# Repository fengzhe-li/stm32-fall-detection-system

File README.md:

# STM32-Based Elderly Fall Detection and Health Monitoring System

A wearable safety device built on the **STM32F103C8T6**: it detects falls via accelerometer, monitors heart rate / SpO₂ / body temperature, and automatically sends an SMS alert with GPS location to a caregiver. Includes a manual SOS button, on-device threshold configuration, and remote SMS commands.

---

## 🎥 Physical Prototype Demonstration

▶️ **[Watch the physical prototype video](docs/videos/physical-prototype.mp4)**

The assembled hardware in operation — OLED display, sensors, GSM/GPS modules, keypad, and a physical fall/recovery cycle with the resulting alert behavior. This is historical evidence from the original build; see [Validation](#-validation) for what it does and does not confirm about the current firmware.

---

## 📌 Overview

The system integrates multiple sensors to monitor an elderly user's physiological state and motion in real time. On a fall or an abnormal vital sign, it sounds a local buzzer and sends an SMS alert containing current vitals and GPS coordinates. A short, fixed confirmation delay after a detected fall gives the wearer a chance to recover or cancel before the alert is sent.

## ⚙️ Features

- Fall detection with hysteresis (separate entry/recovery thresholds) and a fixed confirmation delay before alerting
- Automatic SMS alert on fall, abnormal heart rate, abnormal SpO₂, abnormal temperature, or manual SOS — each tracked independently
- GPS location embedded in every alert (hemisphere-aware coordinate sign)
- Cancel/acknowledge button that silences the buzzer and suppresses the current fall alert, without disabling future fall detection
- On-device OLED UI for live vitals, threshold configuration, and phone-number entry
- Remote SMS commands: request current data on demand, set the alert phone number remotely
- Persistent phone-number storage across power cycles (on-chip Flash)

## 🧩 Firmware & Architecture

Firmware source is available under [`firmware/`](firmware/) (`User/`, `Libraries/`, `Project/` — Keil MDK / ARM Compiler 5, ST Standard Peripheral Library, no HAL/RTOS).

Full architecture write-up — hardware modules, super-loop/interrupt structure, and the fall / health-alert / SOS-cancel flows — is in **[`docs/architecture.md`](docs/architecture.md)**.

## 🔧 Engineering Improvements

The recovered source underwent a memory-safety and control-logic hardening pass: Flash byte/halfword correction, UART/GPS receive-buffer protection, safer coordinate formatting, a GPS hemisphere-sign fix, a MAX30102 divide-by-zero guard, a cancel-alarm control-logic correction, and a bounded GSM startup retry.

Full write-up: **[`docs/engineering-improvements.md`](docs/engineering-improvements.md)**.

## ✅ Validation

Two distinct kinds of evidence exist for this project — **historical physical/simulation validation** of the original build, and **current host-side automated verification** (Clang + ASan/UBSan) of the hardening work above. They are kept clearly separate, and the hardened firmware has **not** yet been rebuilt in Keil, flashed, or re-validated on the physical device.

Full breakdown: **[`docs/validation.md`](docs/validation.md)**.

---

## 🧪 Experimental Results

| Working state | Fall & recovery | Heart-rate sensor active |
|---|---|---|
|  |  |  |

**SMS alerts received:**

| Fall | SOS / help | Heart rate | Blood oxygen | Temperature |
|---|---|---|---|---|
|  |  |  |  |  |

**On-device threshold settings:**

| Heart rate | Blood oxygen | Body temperature | Phone number |
|---|---|---|---|
|  |  |  |  |

## 📍 GPS Positioning Test

Indoor environments cannot receive satellite signals, so latitude/longitude cannot be displayed indoors; in open outdoor environments, GPS coordinates are obtained normally.

## 🖥️ Proteus Simulation

▶️ **[Watch the Proteus simulation video](docs/videos/proteus-simulation.mp4)**  ·  

## 🔌 Circuit / Architecture References

| Circuit schematic | GSM & GPS display | SIM800 power supply |
|---|---|---|
|  |  |  |

## 🧭 Original PCB Layout

This is a screenshot of the original PCB layout created in the design software for the final prototype and preserved in Figure 13 of the dissertation.

---

## 📂 Repository Structure

```
stm32-fall-detection-system/
├── README.md
├── firmware/            # STM32 firmware source (User, Libraries, Project — Keil MDK)
├── hardware/            # Schematic / PCB design files (reference only, see notice below)
├── bom/                 # Bill of materials
├── docs/
│   ├── images/          # Photos, PCB evidence, OLED/UI, and SMS alert screenshots
│   ├── videos/          # Physical prototype + Proteus simulation videos
│   ├── architecture.md
│   ├── validation.md
│   ├── engineering-improvements.md
│   └── U2180177 Li Fengzhe Final report.pdf
└── tests/               # Host-side verification scripts (Clang + ASan/UBSan)
```

## ⚠️ Hardware Files Notice

The `hardware/` folder contains schematic and PCB design files created during development. The dissertation PCB figure above provides direct visual evidence of the final board arrangement. The supplied engineering files should be checked against the dissertation figure and photographed prototype before fabrication.

## 📦 Bill of Materials

Component list: [`bom/list.xlsx`](bom/list.xlsx)

## 📄 Project Report

Full project dissertation: [`docs/U2180177 Li Fengzhe Final report.pdf`](docs/U2180177%20Li%20Fengzhe%20Final%20report.pdf)

## 👨‍💻 Author

**Fengzhe Li** — Embedded Systems | STM32 | IoT

## Reconstructed final-style PCB

**Reconstructed Design Based on the Final Physical Prototype — Not Fabrication-Validated.** The editable KiCad project is in [`hardware/reconstructed-final/Reconstructed_Final_Design/`](hardware/reconstructed-final/Reconstructed_Final_Design/). It contains a symbol-and-wire schematic, routed two-layer PCB, explicit connectivity/BOM evidence and engineering front/back previews. Native KiCad ERC/DRC and 3D outputs are produced by the reconstruction validation workflow and remain subject to review.

The layout follows the genuine [prototype photograph](docs/images/Photograph%20of%20the%20device.jpg): central Blue Pill, GPS/OLED at left, SIM800 at upper-right, sensors below and five buttons at lower-right. Recovered CAD files are supporting historical evidence and remain unchanged. See the [reconstruction report](hardware/reconstructed-final/Reconstructed_Final_Design/RECONSTRUCTION_REPORT.md), [firmware-to-net mapping](hardware/reconstructed-final/Reconstructed_Final_Design/firmware_to_net_mapping.csv) and [verification results](hardware/reconstructed-final/Reconstructed_Final_Design/verification_results.md).

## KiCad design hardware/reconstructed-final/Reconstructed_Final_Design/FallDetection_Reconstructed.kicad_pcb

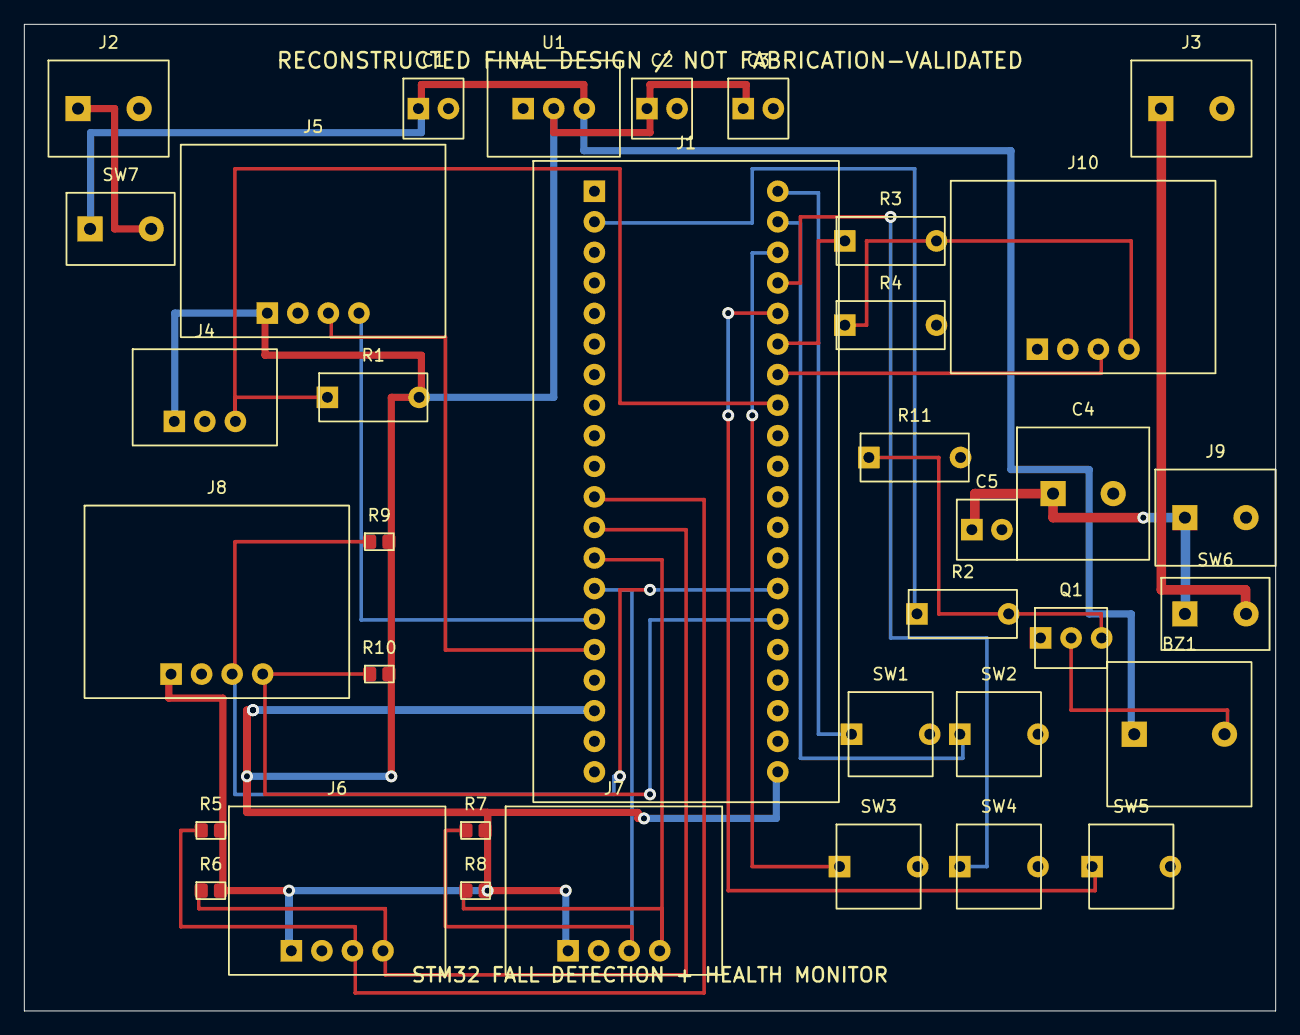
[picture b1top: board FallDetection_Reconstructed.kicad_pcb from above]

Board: 2 copper layers, 104.0 x 82.0 mm, 36 parts (0 on the bottom side), 26 nets.

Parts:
BZ1: 5 V active buzzer; buzzer_2P
C1: 10 uF regulator input; capacitor_2P
C2: 10 uF regulator output; capacitor_2P
C3: 100 nF regulator bypass; capacitor_2P
C4: 1000 uF low-ESR SIM800 bulk; capacitor_large_2P
C5: 100 nF SIM800 bypass; capacitor_2P
J1: STM32F103C8T6 Blue Pill socket; controller_40P
J2: Main 5 V input; power_2P
J3: SIM800 4.0 V input; power_2P
J4: DS18B20 module; temp_sensor_3P
J5: VK2828U7G5LF GPS module; module_4P
J6: ADXL345 breakout; sensor_4P
J7: MAX30102 breakout; sensor_4P
J8: 0.96 inch OLED I2C module; module_4P
J9: SIM800 power header; power_2P
J10: SIM800 UART / PWRKEY header; module_4P
Q1: S8050 low-side buzzer driver; transistor_3P
R1: 4.7k DS18B20 pull-up (DNP if module fitted); resistor_2P
R2: 1k buzzer base resistor; resistor_2P
R3: 10k SIM800 RX divider upper; resistor_2P
R4: 47k SIM800 RX divider lower; resistor_2P
R5: 4.7k ADXL SCL pull-up (DNP); resistor_smd_2P
R6: 4.7k ADXL SDA pull-up (DNP); resistor_smd_2P
R7: 4.7k MAX SCL pull-up (DNP); resistor_smd_2P
R8: 4.7k MAX SDA pull-up (DNP); resistor_smd_2P
R9: 4.7k OLED SCL pull-up (DNP); resistor_smd_2P
R10: 4.7k OLED SDA pull-up (DNP); resistor_smd_2P
R11: 10k buzzer base pull-down; resistor_2P
SW1: Mode button; button_2P
SW2: Up button; button_2P
SW3: Down button; button_2P
SW4: Next button; button_2P
SW5: Help button; button_2P
SW6: GSM VBAT switch; switch_2P
SW7: Main power switch; switch_2P
U1: AMS1117-3.3 regulator module; regulator_3P

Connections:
3V3: C2.1, C3.1, J1.18, J1.40, J4.1, J5.1, J6.1, J7.1, J8.1, R1.2, R5.2, R6.2, R7.2, R8.2, R9.2, R10.2, U1.2
+5V: BZ1.1, C1.1, SW7.1, U1.3
+5V_INPUT: J2.1, SW7.2
ACCEL_SCL_PA6: J1.11, J6.3, R5.1
ACCEL_SDA_PA7: J1.12, J6.4, R6.1
BTN_DOWN_PB14: J1.23, SW3.1
BTN_HELP_PA8: J1.25, SW5.1
BTN_MODE_PB12: J1.21, SW1.1
BTN_NEXT_PB15: J1.24, SW4.1
BTN_UP_PB13: J1.22, SW2.1
BUZZER_BASE: Q1.3, R2.2, R11.1
BUZZER_LOW_SIDE: BZ1.2, Q1.2
BUZZER_PC13: J1.2, R2.1
GND: C1.2, C2.2, C3.2, C4.2, C5.2, J1.19, J1.20, J1.39, J2.2, J3.2, J4.2, J5.2, J6.2, J7.2, J8.2, J9.2, J10.2, Q1.1, R4.2, R11.2, SW1.2, SW2.2, SW3.2, SW4.2, SW5.2, U1.1
GPS_RX_FROM_MCU_TX_PB10: J1.15, J5.4
GPS_TX_TO_MCU_RX_PB11: J1.16, J5.3
GSM_RX_DIVIDED: J10.4, R3.2, R4.1
GSM_TX_FROM_MCU_PA9: J1.26, R3.1
GSM_TX_TO_MCU_RX_PA10: J1.27, J10.3
MAX_SCL_PB1: J1.14, J7.3, R7.1
MAX_SDA_PB0: J1.13, J7.4, R8.1
OLED_SCL_PB6: J1.34, J8.3, R9.1
OLED_SDA_PB7: J1.35, J8.4, R10.1
SIM_VBAT: C4.1, C5.1, J9.1, SW6.1
SIM_VBAT_INPUT: J3.1, SW6.2
TEMP_DQ_PA11: J1.28, J4.3, R1.1

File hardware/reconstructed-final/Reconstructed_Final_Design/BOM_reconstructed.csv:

Reference,Component / module,Qty,Footprint,Population,Evidence / assumption
J1,STM32F103C8T6 Blue Pill socket,1,Reconstruction:controller_40P,Populate,See RECONSTRUCTION_REPORT.md; module dimensions and connector pin order require build review.
J2,Main 5 V input,1,Reconstruction:power_2P,Populate,See RECONSTRUCTION_REPORT.md; module dimensions and connector pin order require build review.
J3,SIM800 4.0 V input,1,Reconstruction:power_2P,Populate,See RECONSTRUCTION_REPORT.md; module dimensions and connector pin order require build review.
J4,DS18B20 module,1,Reconstruction:temp_sensor_3P,Populate,See RECONSTRUCTION_REPORT.md; module dimensions and connector pin order require build review.
J5,VK2828U7G5LF GPS module,1,Reconstruction:module_4P,Populate,See RECONSTRUCTION_REPORT.md; module dimensions and connector pin order require build review.
J6,ADXL345 breakout,1,Reconstruction:sensor_4P,Populate,See RECONSTRUCTION_REPORT.md; module dimensions and connector pin order require build review.
J7,MAX30102 breakout,1,Reconstruction:sensor_4P,Populate,See RECONSTRUCTION_REPORT.md; module dimensions and connector pin order require build review.
J8,0.96 inch OLED I2C module,1,Reconstruction:module_4P,Populate,See RECONSTRUCTION_REPORT.md; module dimensions and connector pin order require build review.
J9,SIM800 power header,1,Reconstruction:power_2P,Populate,See RECONSTRUCTION_REPORT.md; module dimensions and connector pin order require build review.
J10,SIM800 UART / PWRKEY header,1,Reconstruction:module_4P,Populate,See RECONSTRUCTION_REPORT.md; module dimensions and connector pin order require build review.
SW1,Mode button,1,Reconstruction:button_2P,Populate,See RECONSTRUCTION_REPORT.md; module dimensions and connector pin order require build review.
SW2,Up button,1,Reconstruction:button_2P,Populate,See RECONSTRUCTION_REPORT.md; module dimensions and connector pin order require build review.
SW3,Down button,1,Reconstruction:button_2P,Populate,See RECONSTRUCTION_REPORT.md; module dimensions and connector pin order require build review.
SW4,Next button,1,Reconstruction:button_2P,Populate,See RECONSTRUCTION_REPORT.md; module dimensions and connector pin order require build review.
SW5,Help button,1,Reconstruction:button_2P,Populate,See RECONSTRUCTION_REPORT.md; module dimensions and connector pin order require build review.
SW6,GSM VBAT switch,1,Reconstruction:switch_2P,Populate,See RECONSTRUCTION_REPORT.md; module dimensions and connector pin order require build review.
SW7,Main power switch,1,Reconstruction:switch_2P,Populate,See RECONSTRUCTION_REPORT.md; module dimensions and connector pin order require build review.
R1,4.7k DS18B20 pull-up (DNP if module fitted),1,Reconstruction:resistor_2P,DNP,See RECONSTRUCTION_REPORT.md; module dimensions and connector pin order require build review.
R2,1k buzzer base resistor,1,Reconstruction:resistor_2P,Populate,See RECONSTRUCTION_REPORT.md; module dimensions and connector pin order require build review.
R3,10k SIM800 RX divider upper,1,Reconstruction:resistor_2P,Populate,See RECONSTRUCTION_REPORT.md; module dimensions and connector pin order require build review.
R4,47k SIM800 RX divider lower,1,Reconstruction:resistor_2P,Populate,See RECONSTRUCTION_REPORT.md; module dimensions and connector pin order require build review.
R5,4.7k ADXL SCL pull-up (DNP),1,Reconstruction:resistor_smd_2P,DNP,See RECONSTRUCTION_REPORT.md; module dimensions and connector pin order require build review.
R6,4.7k ADXL SDA pull-up (DNP),1,Reconstruction:resistor_smd_2P,DNP,See RECONSTRUCTION_REPORT.md; module dimensions and connector pin order require build review.
R7,4.7k MAX SCL pull-up (DNP),1,Reconstruction:resistor_smd_2P,DNP,See RECONSTRUCTION_REPORT.md; module dimensions and connector pin order require build review.
R8,4.7k MAX SDA pull-up (DNP),1,Reconstruction:resistor_smd_2P,DNP,See RECONSTRUCTION_REPORT.md; module dimensions and connector pin order require build review.
R9,4.7k OLED SCL pull-up (DNP),1,Reconstruction:resistor_smd_2P,DNP,See RECONSTRUCTION_REPORT.md; module dimensions and connector pin order require build review.
R10,4.7k OLED SDA pull-up (DNP),1,Reconstruction:resistor_smd_2P,DNP,See RECONSTRUCTION_REPORT.md; module dimensions and connector pin order require build review.
R11,10k buzzer base pull-down,1,Reconstruction:resistor_2P,Populate,See RECONSTRUCTION_REPORT.md; module dimensions and connector pin order require build review.
Q1,S8050 low-side buzzer driver,1,Reconstruction:transistor_3P,Populate,See RECONSTRUCTION_REPORT.md; module dimensions and connector pin order require build review.
BZ1,5 V active buzzer,1,Reconstruction:buzzer_2P,Populate,See RECONSTRUCTION_REPORT.md; module dimensions and connector pin order require build review.
U1,AMS1117-3.3 regulator module,1,Reconstruction:regulator_3P,Populate,See RECONSTRUCTION_REPORT.md; module dimensions and connector pin order require build review.
C1,10 uF regulator input,1,Reconstruction:capacitor_2P,Populate,See RECONSTRUCTION_REPORT.md; module dimensions and connector pin order require build review.
C2,10 uF regulator output,1,Reconstruction:capacitor_2P,Populate,See RECONSTRUCTION_REPORT.md; module dimensions and connector pin order require build review.
C3,100 nF regulator bypass,1,Reconstruction:capacitor_2P,Populate,See RECONSTRUCTION_REPORT.md; module dimensions and connector pin order require build review.
C4,1000 uF low-ESR SIM800 bulk,1,Reconstruction:capacitor_large_2P,Populate,See RECONSTRUCTION_REPORT.md; module dimensions and connector pin order require build review.
C5,100 nF SIM800 bypass,1,Reconstruction:capacitor_2P,Populate,See RECONSTRUCTION_REPORT.md; module dimensions and connector pin order require build review.

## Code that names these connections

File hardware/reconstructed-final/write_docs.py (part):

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

mapping_rows = [
    ("GPS TX → MCU RX", "PB11 / USART3_RX", "GPS_TX_TO_MCU_RX_PB11", "usart3.c configures PB11 as RX", "Confirmed from active firmware", "PB11 is not used for the active buzzer path."),
    ("GPS RX ← MCU TX", "PB10 / USART3_TX", "GPS_RX_FROM_MCU_TX_PB10", "usart3.c configures PB10 as TX", "Confirmed from active firmware", "Blue Pill header pin 15 only; erroneous baseline tie to header pin 38 removed."),
    ("GSM TX → MCU RX", "PA10 / USART1_RX", "GSM_TX_TO_MCU_RX_PA10", "usart1.c GPIO and USART setup", "Confirmed from active firmware", "SIM800 TX logic level is normally accepted by STM32 3.3 V input."),
    ("GSM RX ← MCU TX", "PA9 / USART1_TX", "GSM_TX_FROM_MCU_PA9 → 10k/47k divider → GSM_RX_DIVIDED", "usart1.c GPIO and USART setup", "Firmware pin confirmed; divider is a new design decision", "Divider targets about 2.72 V from 3.3 V for a bare 2.8 V SIM800 UART input."),
    ("Buzzer driver", "PC13", "BUZZER_PC13", "main.c uses BEEP from key.h; KEY_Init configures PC13", "Confirmed from active startup path", "PB11 BEEP_GPIO_Config in led.c is not called. S8050 lead order remains footprint-dependent."),
    ("ADXL345 SCL / SDA", "PA6 / PA7", "ACCEL_SCL_PA6 / ACCEL_SDA_PA7", "iic.c and iic.h; main calls IIC_init", "Confirmed from active firmware", "PD5/PD6 appears only in a stale comment. Optional pull-ups are DNP by default."),
    ("MAX30102 SCL / SDA", "PB1 / PB0", "MAX_SCL_PB1 / MAX_SDA_PB0", "myiic.c; main calls bsp_InitI2C", "Confirmed from active firmware", "Optional pull-ups are DNP by default because breakout pull-ups are unresolved."),
    ("OLED SCL / SDA", "PB6 / PB7", "OLED_SCL_PB6 / OLED_SDA_PB7", "OLED_I2C.c; main calls OLED_Init", "Confirmed from active firmware", "Optional pull-ups are DNP by default."),
    ("DS18B20 DQ", "PA11", "TEMP_DQ_PA11", "ds18b20.c; dissertation", "Confirmed from active firmware", "4.7k carrier pull-up is DNP if the fitted module already has one."),
    ("Buttons", "PB12, PB13, PB14, PB15, PA8", "BTN_MODE / BTN_UP / BTN_DOWN / BTN_NEXT / BTN_HELP", "key.c and key.h", "Confirmed from active firmware", "Active-low switches to ground; MCU internal pull-ups are enabled."),
    ("Blue Pill power", "3V3 header pins 18 and 40", "3V3", "Carrier power architecture", "New design decision", "The 5 V header pin 38 is intentionally unconnected. Do not connect USB while the carrier drives 3.3 V."),
    ("SIM800 power", "Separate 4.0 V input", "SIM_VBAT_INPUT / SIM_VBAT", "Prototype photo and dissertation show separate modem supply", "Visual evidence plus new power-integrity design", "0.8 mm routing and 1000 uF low-ESR plus 100 nF local bypass; source must tolerate current bursts."),
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
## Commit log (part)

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2026-03-15 README.md
